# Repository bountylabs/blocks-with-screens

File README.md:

# Blocks With Screens

It's Twitterversary blocks, but with screens and internet. Originally a Fall 2019 Twitter HackWeek project by [@johnboiles](https://github.com/johnboiles), [@magus](https://github.com/magus), [@mikeperiscope](https://github.com/mikeperiscope), [@seanfchan](https://github.com/seanfchan), and [@smartfuse](https://github.com/smartfuse).

## Assembly

### [**Click here to view assembly instructions on YouTube**](https://youtu.be/LxgdhXQPZw0)

Tips, notes & corrections:
* To protect the pins, we're shipping with two of the circuit boards attached to eachother. You'll need to separate these circuit boards before following the instructions above. Just gently pull them apart to separate them. They're hard to break :)
* Some of the boards may have small tabs protruding from the sides which may cause them not to fit in the wooden block. This is a byproduct of the manufacturing process. Clip these tabs off with nail clippers or wire clippers.
* Feel free to ask us on Twitter [@blkswithscreens](https://twitter.com/blkswithscreens) if you have any questions or problems!

## Components

### Blockware

This is the example software that you can run on the blocks. See [blockware/README.md](https://github.com/bountylabs/blocks-with-screens/blob/main/blockware/README.md) for installation instructions and a listing (with gifs!) of the available blockware.

### CAD

This contains the various design files building the block hardware. Most importantly, it contains the [Autodesk Eagle](https://www.autodesk.com/products/eagle/free-download) design files for the 3 PCBs that make up the block. See the [README.md](https://github.com/bountylabs/blocks-with-screens/blob/main/cad/pcb/README.md) in that directory for an overview of the responsibilities of the three different boards.

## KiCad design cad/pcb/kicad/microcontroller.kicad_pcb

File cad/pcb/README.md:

# Blocks With Screens PCB Files

## Components

The blocks are made up of 3 components.

### OLED Board

This board is responsible for all the circuitry to drive a SSD1351 OLED display. This design is heavily based on [Adafruit's breakout board](https://github.com/adafruit/Adafruit-1.5inch-Color-OLED-PCB) for the same display.

It consists of a 13V boost regulator to provide the required voltage to drive the OLED, as well as necessary passive components required by the OLED's datasheet.

### Microcontroller Board

This board is a mounting point for the ESP12 microcontroller and the MMA8452Q 3-axis accelerometer. It also has unpopulated pads for a [SparkFun Qwiic](https://www.sparkfun.com/qwiic) connector and a WS2812B RGB LED if you want to add additional functionality.

### USB Board

This board is responsible for:
* Providing a USB serial interface for programming the microcontroller (with automatic reset)
* Providing regulated 3.3V power to the Microcontroller and OLED
* Providing charging circuitry to charge the LiPo battery

This board is based on various Adafruit [LiPo charging boards](https://learn.adafruit.com/adafruit-pro-trinket-lipoly-slash-liion-backpack) and [USB powered boards](https://learn.adafruit.com/introducing-trinket/downloads) with the simplest (by part count) USB-serial chip we could find.

## PCB Hacking

We hope you'll open up your blocks and add new functionality or boards we never even dreamed of.

The pin layout is compatible with the [Wemos D1 Mini](https://docs.wemos.cc/en/latest/d1/d1_mini.html) (available on your usual internet shopping sites) so any shields made for those should work!

There is un unpopulated [SparkFun Qwiic](https://www.sparkfun.com/qwiic) connector on the microcontroller board. If you solder on a Qwiic connector (just a 4-pin JST connector) you can connect your board to any of the dozens of [Qwiic compatible peripherals](https://www.sparkfun.com/qwiic#products) (e.g. sensors, screens, GPS) out there.

There's an unpopulated spot on the Microcontroller board for a WS2812B RGB LED (or similar). This might come in handy if you want to, say, cut a window in the side of your block and trick it out with colors inside. Note that these LEDs will typically initialize to a random color so if you add the LED, but don't use it in your program, it will probably be lit up to a random color.

You could also add PCBs for different microcontrollers, different screens, or maybe even make a USB-C version! This was meant to be modular. Have fun, and share back what you build!

## Manufacturing Boards

We used [OshPark](https://oshpark.com/) for creating our prototype PCBs which we then soldered by hand or in a [reflow oven](https://github.com/UnifiedEngineering/T-962-improvements). We used [PCBWay](https://www.pcbway.com/) to mass manufacture assembled PCBs.

There's an included [script](https://github.com/bountylabs/blocks-with-screens/blob/main/pcb/eagle_to_pcbway.py) for exporting the Eagle PCB files in a bill-of-materials (BOM) format that PCBWay accepts.

## Changelog

### Microcontroller Board V4

* MMA8452QR1 accelerometers are #chipshortage'd. Switch to LIS2DW12

### OLED Board V5

* Revert the revert to go back to VIN for the 13V boost circuit as it didn't seem to have any effect. And this lightens the load on the 3.3V regulator. This is effectively the same design as OLED Board V3.

### USB Board V5

* Turn the battery connector counter-clockwise by 90 degrees to avoid wires hanging off the side of the board and not fitting in the block.

### OLED Board V4

* Revert back to using 3.3V for the 13V boost circuit to hopefully avoid issues I've seen twice now with the OLED screens developing bad vertical lines of pixels. This is what Adafruit does in their board; perhaps there's a reason for it.

### USB Board V4

* Use thicker (power) trace for 3.3V
* Make the USB side slots wider to comply with PCBWay
* Add a JST-SH connector (SM02B-SRSS-TB) for the battery

### Microcontroller Board V3

* Attach 3.3V to the ESP12 (doh!)

### OLED Board V3

* Uses `D4/GPIO2` for `OLED DC` instead of `D1/GPIO5` since that pin is I2C `SCK`.

### Microcontroller Board V2

* Fixed disconnected decoupling capacitor.
* Added optional header for MMA8452QR1 accelerometer.
* Added optional [Qwiic](https://www.sparkfun.com/qwiic) header for SparkFun accessories.
* Added optional [5050 NeoPixel](https://www.adafruit.com/product/1655) pad.

### USB Board V3

* Fix width of power trace going to the switch.

### OLED Board V2

* Uses `D1` for `OLED DC` instead of `D6` (`MISO`) so we don’t have to hack SPI.c for hardware SPI.
* Uses `VIN` for power for the 13V boost (possible this will reduce the flicker, especially during low battery).
* Removed the 3-pin SPI jumper since we didn’t use it.
* Move all the screen capacitors closer to the screen connector (even smaller chance of reducing flicker)

### USB Board V2

* Removed oscillator and move to using the `CH340C` instead of `CH340G` USB-UART chip.
* Connect `VCC` on the `CH340C` chip (fix error from V1).
* Move most parts to the front of the board for easier manufacturing.
* Add an optional on LED.
* Add pads for a switch.

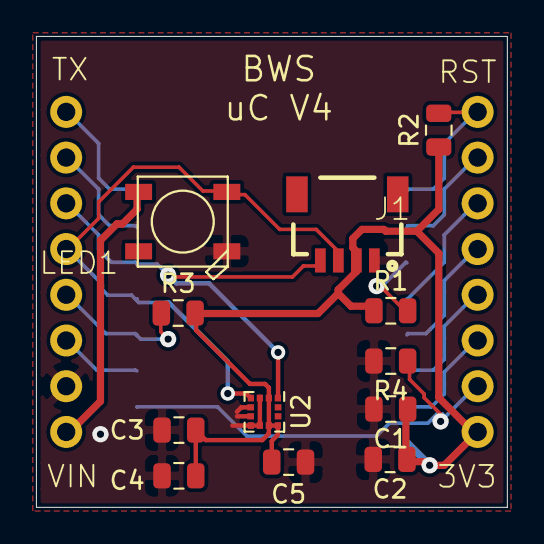
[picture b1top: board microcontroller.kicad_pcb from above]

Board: 2 copper layers, 26.2 x 26.2 mm, 15 parts (0 on the bottom side), 17 nets.

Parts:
C1, C4: 10uF; C_0805_2012Metric
C2: .1uF; C_0805_2012Metric
C3, C5: 100nF; C_0805_2012Metric
J1: SMD; 1X04_1MM_RA
JP1, JP2: PINHD-1X8CLEANBIG; 1X08-CLEANBIG
LED1: WS2812B5050; WS2812B
R1, R2, R3, R4: 10K; R_0805_2012Metric
U2: LIS2DW12; LGA-12_2x2mm_P0.5mm
X1: ESP-12

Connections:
3.3V: C1.1, C2.1, C3.2, C4.2, C5.1, J1.2, JP2.1, R1.1, R2.1, R3.2, U2.2, U2.9, U2.10, X1.8
/A0: JP2.7, X1.2
/CH_PD: R1.2, X1.3
/D0/GPIO16: JP2.6, X1.4
/D1/GPIO5/SCL: J1.4, JP1.3, U2.1, X1.14
/D2/GPIO4/SDA: J1.3, JP1.4, LED1.4-DIN, U2.4, X1.13
/D3/GPIO0: JP1.5, R3.1, X1.12
/D4/GPIO2: JP1.6, X1.11
/D5/GPIO14/SCK: JP2.5, X1.5
/D6/GPIO12/MISO: JP2.4, X1.6
/D7/GPIO13/MOSI: JP2.3, X1.7
/D8/GPIO15: JP2.2, R4.1, X1.10
/RESET: JP2.8, R2.2, X1.1
/RX: JP1.2, X1.15
/TX: JP1.1, X1.16
GND: C1.2, C2.2, C3.1, C4.1, C5.2, J1.1, JP1.7, LED1.3-GND, R4.2, U2.3, U2.5, U2.6, U2.7, U2.8, X1.9
VIN: JP1.8, LED1.1-VDD

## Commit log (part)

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2019-09-18 oled board ready to be fab'd
2019-09-18 microcontroller board ready to be fab'd
2019-09-23 initial video api
2019-09-23 read/write fs
2019-09-23 yarn add -D now
2019-09-23 --prod target deprecated
2019-09-23 null data if block not written
2019-09-23 convert uint8 rgba to uint16 rgb
2019-09-24 input to canvas raf for video
2019-09-24 notes to self
2019-09-24 yarn start
2019-09-24 camera capture
2019-09-24 offscreen video
2019-09-24 visible preview
2019-09-24 natural width and height
2019-09-24 fit into canvas
2019-09-24 fill option
2019-09-24 rotate option
2019-09-24 setTransform rotate
2019-09-24 break up 2 bytes comments
2019-09-24 debug with block 3
2019-09-25 hardcoded content length and no transfer encoding chunked
2019-09-25 seans test remove file
2019-09-25 Beginning of the passive info sketch
2019-09-25 Successfully getting realtime weather information
2019-09-25 Converted to Platform IO project
2019-09-25 Move headers to the correct folder
2019-09-25 Link PCBs with Fusion360 design
2019-09-25 Added Snake
2019-09-25 cwd path
2019-09-25 blockswithscreens-app
2019-09-25 Not a completely working implementation of stock
    The response from alpha vantage is working but the response is way to big fit in RAM. Will need to figure out how to parse in stream? or might have to make a banckend server that just sends us only t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
2019-09-25 tools for http-udp bridge
2019-09-26 custom now routes for static
2019-09-26 weather endpoint done
    Takes data from source and transforms it to provide just the data that we need.
2019-09-26 Start of BlockChainWithScreens
    Ktor backend to serve clients so we can fine tune resposnes for the resources constrained clients.
2019-09-26 Stop committing secret api keys
2019-09-26 Add an example of JPEG downloading
2019-09-26 server: mimic now.json routes for local dev
2019-09-26 libgif.js
2019-09-26 tiny jsgif canvas
2019-09-26 now: serve js files
2019-09-26 chipset rgb565le
2019-09-26 api/gif: john gif idea
2019-09-26 working update for screen
2019-09-26 udp client
2019-09-26 video-display first commit
2019-09-26 secrets file
2019-09-27 added tcp option
2019-09-27 rgb565 endpoint
2019-09-27 create the real weather icon url
2019-09-27 Microcontroller is now talking to our backend server
2019-09-27 https
2019-09-27 styling website
2019-09-27 server mimic now.json later
2019-09-27 gif parse loading match card height
2019-09-27 VSCode really wants this .gitignore here
2019-09-27 server normal in prod
2019-09-27 Now serving weather image assets in jpg
2019-09-27 extra “/“ LAME!!!
2019-09-27 env vars
2019-09-27 remove blockswithscreens
2019-09-27 Image is now downloading and rendering for the weather app
2019-09-27 ON_GCLOUD static host
2019-09-27 Gif download example
2019-09-27 Tweaks to gif player
2019-09-27 static assets locally
2019-09-29 Blockware for showing Home Assistant states
2019-09-29 More bootup formatting nits
2019-09-29 More nits -- global naming and only blanking the screen as needed
2019-10-01 Explicitly include libraries in passiveinfo platform.ini
2019-10-03 Support for chunked encoding in gif-example
2019-10-04 gif and video api 404 when no memory at block param
2019-10-04 server api cleanup
2019-10-05 Prototype of gif qr code downloading
2019-10-08 note to path to modify for MISO pin fix
2019-10-10 README: fix miso pin and 90fps docs
2019-10-10 90fps
2019-10-11 Backlink to CADLAB.io has been added.
2019-10-11 curvy-snake
2019-10-13 OTAUpdates classy header method names
2019-10-13 CurvySnake: refactor GameStructs
2019-10-14 Colors: RGB565 (RGB888 to RGB565)
2019-10-14 debugging RGB565
2019-10-14 GameStructs: Entity class
2019-10-14 Colors: randomColor
2019-10-14 OTAUpdates: output for connect .
2019-10-14 .clang-format
2019-10-14 CurvySnake: use Entity.h
2019-10-14 OTAUpdates: README
2019-10-14 OTAUpdates: progress for ota update
2019-10-15 Reorganize directory structure
2019-10-15 Set up homeassistant example to use share OTA library
2019-10-15 Travis CI build
2019-10-15 Fix qrcode include for case-sensitive file systems
2019-10-15 Rename secrets.example.h to secrets.h.example
2019-10-15 ../libs lgtm
2019-10-15 inverse mass for physics
2019-10-15 Inline Colors and Random methods
    So that they only get compiled in when they are used.
2019-10-15 More shared library usage in homeassistant-display
2019-10-15 Decomposing libraries a bit more
2019-10-15 Add Travis badge to README.md
2019-10-16 CartesianXY > Vec2
2019-10-16 Entity: use Vec2d
2019-10-16 lib/Vec2d
2019-10-16 Vec2d: ; and round out operators
2019-10-16 Random: float for memory
2019-10-16 Fix outputf
2019-10-16 Rename WiFi->WifiHelper to prevent platformio from getting confused
2019-10-17 curvy-snake: README
2019-10-17 bouncing-logo project
2019-10-17 bouncing-logo: +demo gif
2019-10-17 Run tests for bouncing-logo
2019-10-17 bouncing-logo: demo
2019-10-19 set up udp receiver
2019-10-22 USB board schematic V2 done
2019-10-22 Add a bunch of manufacturer part numbers to OLED board
2019-10-22 Add manufacturer part numbers to USB board
2019-10-22 Use GPIO2 instead of GPIO5(SCL) for OLED DC pin
2019-10-22 Rework Oled board to use VIN
2019-10-22 V2 usb board ordered
2019-10-22 Add a pcb/README.md with details about board changes
2019-10-22 TLLogos.h
2019-10-23 Mark updated usb v3 board (ordered)
2019-10-23 Oled board v3 ordered
2019-10-23 Add part numbers for the headers on the usb board
2020-03-31 Bump next from 9.0.6 to 9.3.2 in /web/image-video-converter
    Bumps [next](https://github.com/zeit/next.js) from 9.0.6 to 9.3.2.
    - [Release notes](https://github.com/zeit/next.js/releases)
    - [Commits](https://github.com/zeit/next.js/compare/v9.0.6...v9.3.2)
2020-05-20 added conversion script for pcbway manufacturing
2020-06-26 Use POWER net class (thicker trace) for 3.3V in USB board
2020-06-26 Make the slots for the usb connector wider
2020-06-27 Fix microcontroller board to actually connect 3.3V to the microcontroller
2020-06-27 Add example of using the RGB LED
2020-06-30 Remove switch bypass jumper (revert c81c233)
2020-06-30 Bump USB board silkscreen to V4
2020-06-30 Updates for V4 of USB board
2020-06-30 Center battery connector at top of usb board
2020-07-01 Headers were on the wrong side on the usb board
2020-07-01 Fix 3d models for microcontroller board
2020-07-02 Rotate switch so that pin numbering matches orientation from the datasheet
2020-07-02 added thru-hole parameters and updated eagle export script
2020-07-02 added thru-hole prop to usb board
2020-07-02 added populate attr
2020-07-02 changed some part numbers
2020-07-02 added MPN for jst connector
2020-07-03 Add accelerometer + Adafruit Pixel Dust demo
2020-07-04 Add rgb-accelerometer demo and make a lot of demos use DefaultConfig.h
2020-07-07 updated part number for usb connector
2020-07-08 added 8 pin header part number
2020-07-09 changed part number for pin header on oled board
2020-07-10 changed 590k resistor to 620k
2020-08-29 USB pcb V5 - turn battery connector 90 deg
2020-11-17 Migrate GitHub Action from master to main
2020-11-17 Giant reorganization and cleanup of all the blockware examples
2020-11-18 Add gifs / images to blockware!
2020-11-18 Add gif to gif-download listing
2020-11-18 Some README.md edits after proofreading the next day
2020-11-19 Blockware programming quickstart and pro-tips
2020-11-21 blockware/README: styling refactor
2020-11-21 Fix comment about hacking SPI on OLED V1 boards
2020-11-22 blockware/twitter-text
2020-11-22 Random: more statics
2020-11-22 blockware/twitter-text: Demo gif
2020-11-23 Details for running the video-display blockware
2020-11-23 Include twitter-text in ci
2020-11-24 Add some notes about running stocks-and-weather
2020-11-24 Update ffmpeg example commands with correct aspect ratio
2020-11-30 www: webgl block demo
2020-11-30 www: webgl shadows
2020-11-30 www: postinstall script for nextjs bug
2020-11-30 www: canvas texture for block screen
2020-11-30 www: VirtualBlox emulation on block
2020-11-30 www: deploy commands
2020-12-02 Move pcb under cad
2020-12-02 Add a dump of the Fusion 360 archive at v90
2020-12-06 change random() to time_random()
2020-12-06 some files needed vector definition
2020-12-06 trying again
2020-12-07 fixed fireworks
2021-03-16 updated R2 and R4 values, changed 3.3v regulator to AP2112K-3.3
2021-03-16 Change reverted OLED to V5. Small GND trace cleanup.
2021-03-16 added POPULATE to usb thru hole parts
2021-03-16 renamed yellow led to white
2021-06-04 added kicad files for microcontroller board v4
2021-06-04 added imported library
2021-10-16 blockware/fireworks
2021-10-18 Untested API migrations to work with the latest esp arduino libs
2021-10-21 fireworks: remove superfluous new lines
2021-11-06 README: Assembly video
2021-11-06 README: build status
2021-11-06 Use johnboiles AdafruitGFX fork
    While we wait for https://github.com/adafruit/Adafruit-GFX-Library/pull/370 to get merged.
    This also removes the 90fps example since it's no longer as relevant.
2021-11-06 messy changes to make LISDW12 accelerometer work with pixel-dust
2021-11-08 moved lis2dw12 files to lib
2021-11-08 set up LIS2DW12 as dependency
2021-11-08 Mhill/lisdw12 accel (#5)
    * messy changes to make LISDW12 accelerometer work with pixel-dust
    * moved lis2dw12 files to lib
    * removed unused accelerometer code
    * set up LIS2DW12 as dependency
2021-11-09 Keep (disabled-by-default) configs for MMA8452Q accelerometer for old blocks
2021-11-11 Update README.md with V2 instructions video (#7)
2021-11-13 ESP32-PICO-D4 based microcontroller board
2021-11-16 Keep (disabled-by-default) configs for MMA8452Q accelerometer for old blocks (#6)
2021-11-16 Fix angle randomization (#9)
    `random` returns a `long`. `random(TAU)` produced an integer between 0 and 6. So the angle of the sparks always came out along the points of a hexagon. By converting to a float before scaling we can 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
2021-11-16 Vblox emscripten 2 (#10)
    * added emscripten stuff
    * change random() to time_random()
    * some files needed vector definition
    * added random.h
    * trying again
    * more random
2021-11-17 Add fancy fireworks, text and logo animations, and sleep mode
2021-11-17 Rename demo gif
2021-11-17 Remove old fireworks project
2021-11-17 Rename fireworks2 dir to fireworks
2021-11-17 Fixes to reintroduce some recent changes
2021-11-17 Replace inttypes with stdint in Color.h
2021-11-18 Tests pass locally
2021-11-18 Don't animate text if it's already in position
2021-11-20 🛠️ build(update): make update and docs
    Ensure PlatformIO is up to date.
    This fixes an issue where the toolchain was not able to build c++17
    which is required in some Blockware now (see blockware/fireworks)
2021-11-21 Local targets to generate SDL2 native blockware builds.
2021-11-22 Fixes from review
2021-11-22 2x the scale when running as native
2021-11-22 🐛fix(pixel-dust): accel->begin returns false always
2021-11-22 camelCase
2021-11-23 Try to fix build
2021-11-23 Update VirtualBlox documentation
2021-11-24 Frame limit native blockware
2021-11-24 Run python-black on VirtualBlox python
2021-11-24 Hook up delay to SDL_Delay
2021-11-24 Fix the build
2021-11-24 Go back to c++17
2021-11-24 Virtualblox accel support (#17)
    * Fix the build
    * VirtualBlox support for LIS2DW12 accelerometer
    * Go back to c++17
2021-11-25 📦feat(VirtualBlox): use UTF8 fork of Adafruit_GFX lib (#18)
2021-11-25 added fork of pixeldust
2021-11-26 Support for building wasm straight from PlatformIO
2021-11-27 connected js to c++
2021-11-27 🧪chore(test): enable blockware/matrix test
2021-11-27 ✨feat(Canvas,FPS): classes for convenience
2021-11-27 🎨feat(Colors): NEON_GREEN
2021-11-27 🧹refactor(matrix): safe_bounded_inc for integers
2021-11-27 ✨feat(matrix) blockware/matrix
    forked adafruit gfx with utf 8 support
    fixed build errors by copying from johnboiles fork
    generated a subset of unifont into program memory
    blockware/matrix/.pio/libdeps/esp12e/Adafruit GFX Library UTF8/glcdfont.c
    japanese characters now work! 🎉
2021-11-27 🧹refactor(matrix): based on pull/16 feedback
2021-11-27 🚀feat(Matrix): infinite pan rain
2021-11-28 use consistent update rate for dust grain position
2021-11-29 change multiplier for accel
2021-11-29 🐛fix(Matrix): int x,y float overlap?
2021-11-29 🐛fix(Matrix): include edge overflow
2022-01-06 ESP32-PICO-D4 based microcontroller board (#13)
2022-08-30 More link-board stuff
